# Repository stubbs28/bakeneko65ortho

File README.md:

# bakeneko65ortho
 ortholinearish layout for the bakeneko65

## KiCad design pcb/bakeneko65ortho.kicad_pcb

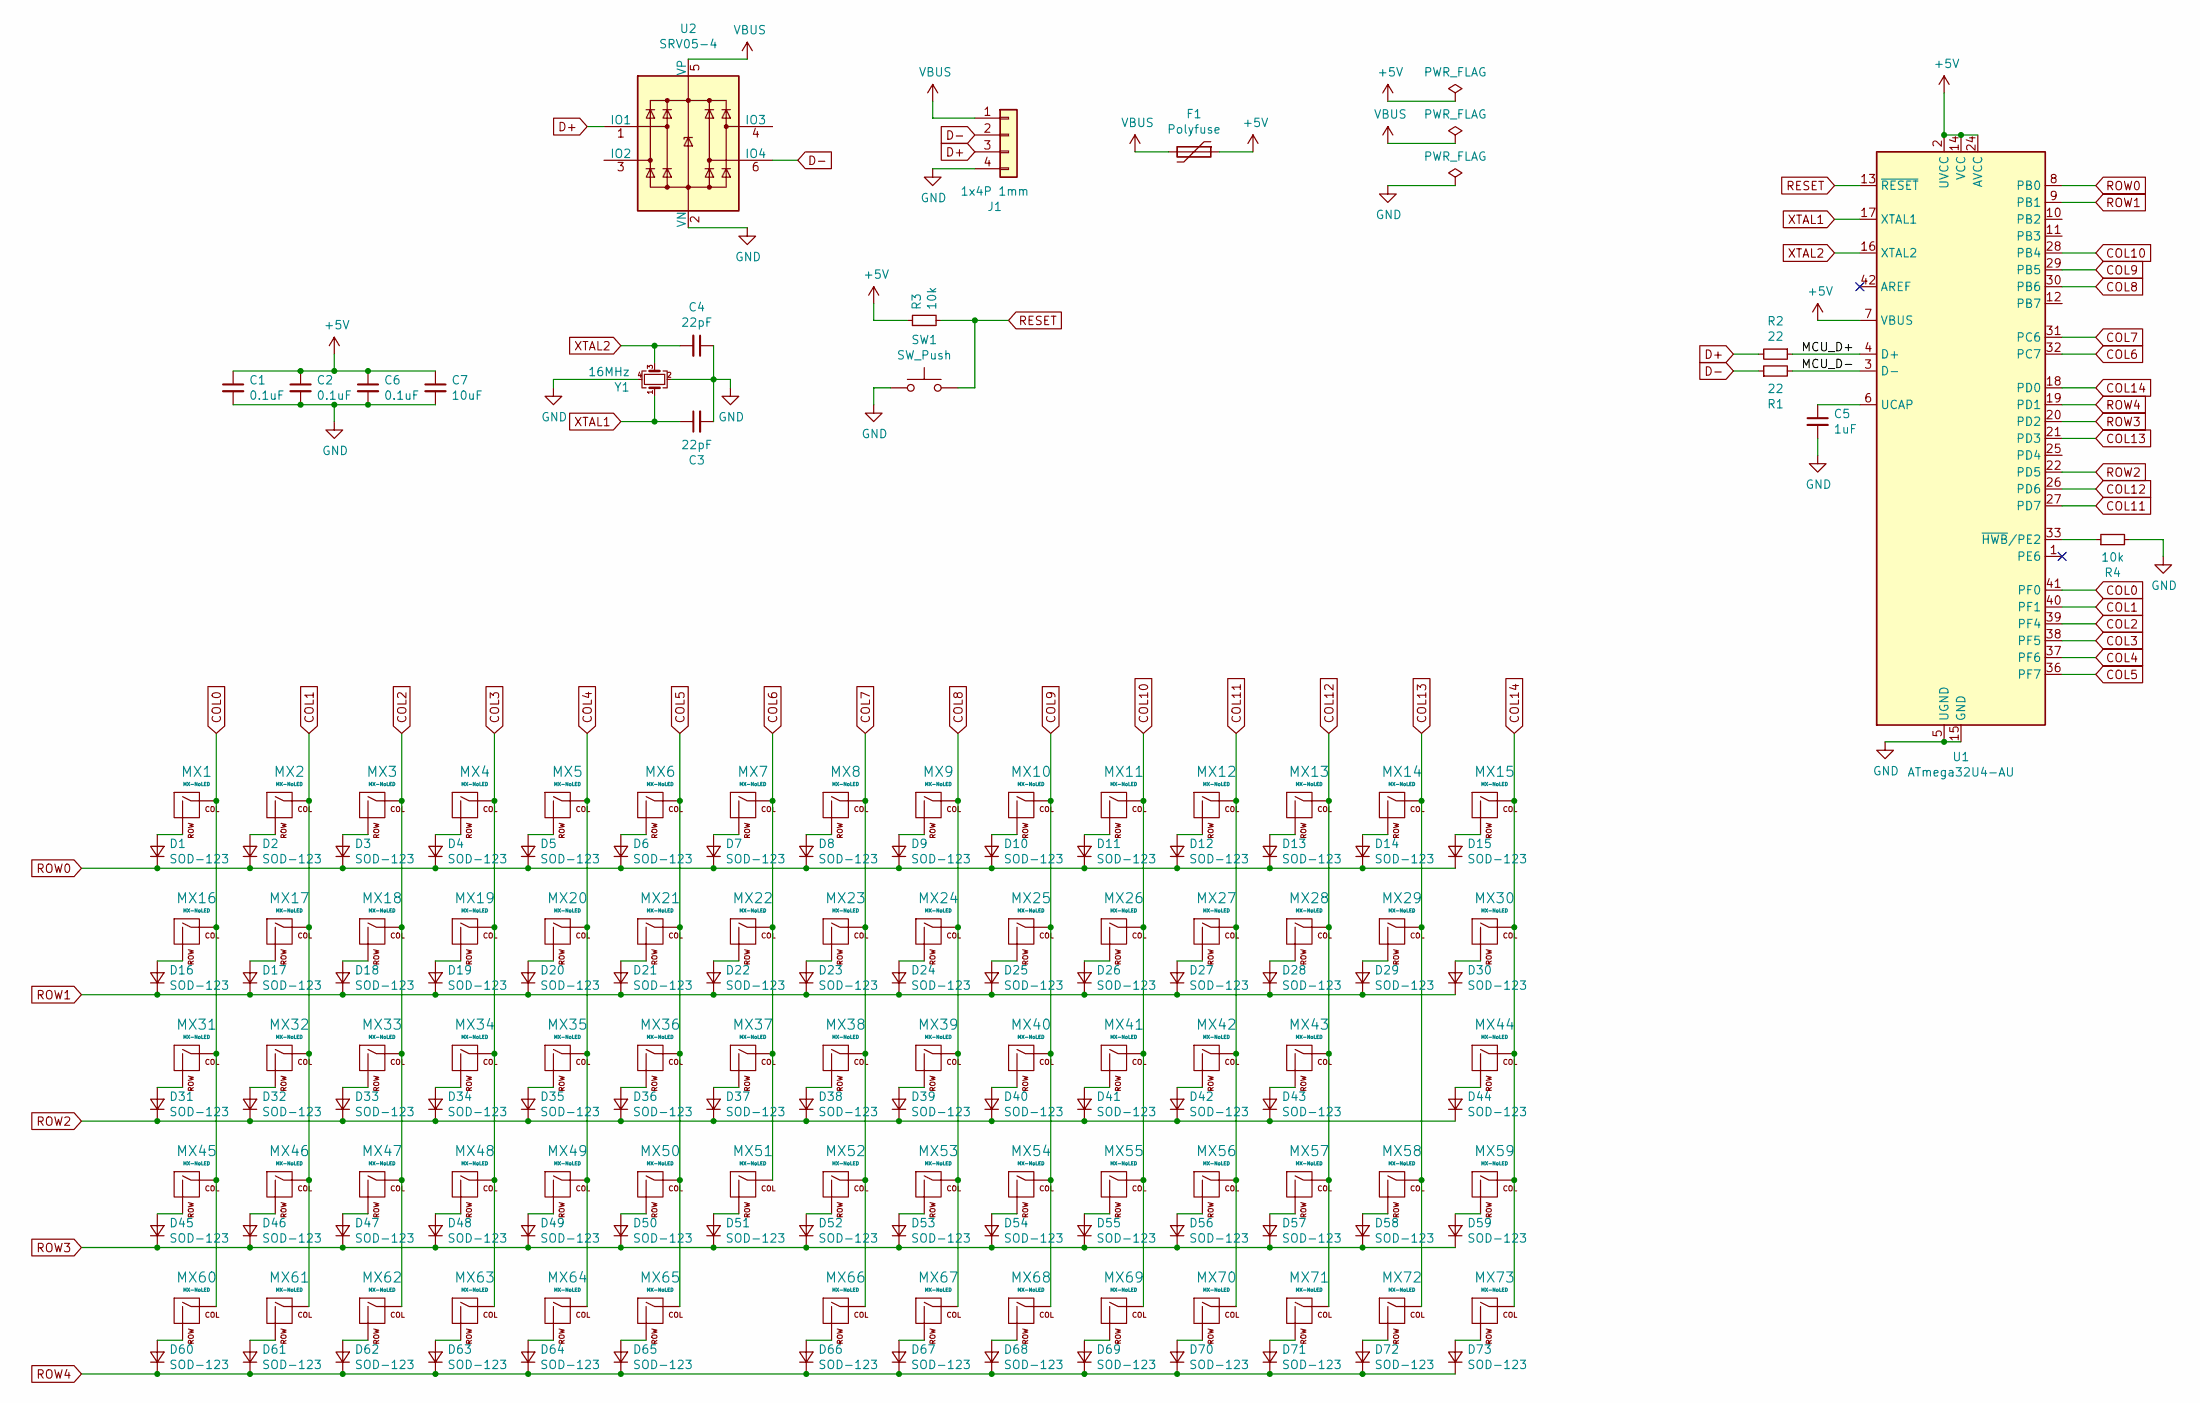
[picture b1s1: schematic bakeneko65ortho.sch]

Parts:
C1, C2, C6: 0.1uF; C_0805_2012Metric
C3, C4: 22pF; C_0805_2012Metric
C5: 1uF; C_0805_2012Metric
C7: 10uF; C_0805_2012Metric
D1, D2, D3, D4, D5, D6, D7, D8, D9, D10, D11, D12, D13, D14, D15, D16, D17, D18, D19, D20, D21, D22, D23, D24, D25, D26, D27, D28, D29, D30, D31, D32, D33, D34, D35, D36, D37, D38, D39, D40, D41, D42, D43, D44, D45, D46, D47, D48, D49, D50, D51, D52, D53, D54, D55, D56, D57, D58, D59, D60, D61, D62, D63, D64, D65, D66, D67, D68, D69, D70, D71, D72, D73: SOD-123; D_SOD-123
F1: Polyfuse; Fuse_1206_3216Metric
J1: 1x4P 1mm; JST_SH_SM04B-SRSS-TB_1x04-1MP_P1.00mm_Horizontal
MX1, MX2, MX3, MX4, MX5, MX6, MX7, MX8, MX9, MX10, MX11, MX12, MX13, MX15, MX16, MX17, MX18, MX19, MX20, MX21, MX22, MX23, MX24, MX25, MX26, MX27, MX28, MX31, MX32, MX33, MX34, MX35, MX36, MX37, MX38, MX39, MX40, MX41, MX42, MX45, MX46, MX47, MX48, MX49, MX50, MX51, MX52, MX53, MX54, MX55, MX56, MX58, MX59, MX60, MX61, MX62, MX63, MX64, MX66, MX67, MX69, MX71, MX72, MX73: MX-NoLED; MXOnly-1U-NoLED
MX14: MX-NoLED; MXOnly-2U-NoLED
MX29, MX30: MX-NoLED; MXOnly-1.5U-NoLED
MX43, MX57: MX-NoLED; MXOnly-2.25U-ReversedStabilizers-NoLED
MX44: MX-NoLED; MXOnly-1.75U-NoLED
MX65: MX-NoLED; MXOnly-2U-ReversedStabilizers-NoLED
MX68, MX70: MX-NoLED; MXOnly-1.25U-NoLED
R1, R2: 22; R_0805_2012Metric
R3, R4: 10k; R_0805_2012Metric
SW1: SW_Push; SKQG-1155865
U1: ATmega32U4-AU; TQFP-44_10x10mm_P0.8mm
U2: SRV05-4; SOT-23-6
Y1: 16MHz; Crystal_SMD_3225-4Pin_3.2x2.5mm

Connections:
+5V: C1.1, C2.1, C6.1, C7.1, F1.1, R3.1, U1.2 (UVCC), U1.7 (VBUS), U1.14 (VCC), U1.24 (AVCC), U1.34 (VCC), U1.44 (AVCC)
/MCU_D+: R2.1, U1.4 (D+)
/MCU_D-: R1.2, U1.3 (D-)
COL0: MX1.1 (COL), MX16.1 (COL), MX31.1 (COL), MX45.1 (COL), MX60.1 (COL), U1.41 (PF0)
COL1: MX2.1 (COL), MX17.1 (COL), MX32.1 (COL), MX46.1 (COL), MX61.1 (COL), U1.40 (PF1)
COL2: MX3.1 (COL), MX18.1 (COL), MX33.1 (COL), MX47.1 (COL), MX62.1 (COL), U1.39 (PF4)
COL3: MX4.1 (COL), MX19.1 (COL), MX34.1 (COL), MX48.1 (COL), MX63.1 (COL), U1.38 (PF5)
COL4: MX5.1 (COL), MX20.1 (COL), MX35.1 (COL), MX49.1 (COL), MX64.1 (COL), U1.37 (PF6)
COL5: MX6.1 (COL), MX21.1 (COL), MX36.1 (COL), MX50.1 (COL), MX65.1 (COL), U1.36 (PF7)
COL6: MX7.1 (COL), MX22.1 (COL), MX37.1 (COL), MX51.1 (COL), U1.32 (PC7)
COL7: MX8.1 (COL), MX23.1 (COL), MX38.1 (COL), MX52.1 (COL), MX66.1 (COL), U1.31 (PC6)
COL8: MX9.1 (COL), MX24.1 (COL), MX39.1 (COL), MX53.1 (COL), MX67.1 (COL), U1.30 (PB6)
COL9: MX10.1 (COL), MX25.1 (COL), MX40.1 (COL), MX54.1 (COL), MX68.1 (COL), U1.29 (PB5)
COL10: MX11.1 (COL), MX26.1 (COL), MX41.1 (COL), MX55.1 (COL), MX69.1 (COL), U1.28 (PB4)
COL11: MX12.1 (COL), MX27.1 (COL), MX42.1 (COL), MX56.1 (COL), MX70.1 (COL), U1.27 (PD7)
COL12: MX13.1 (COL), MX28.1 (COL), MX43.1 (COL), MX57.1 (COL), MX71.1 (COL), U1.26 (PD6)
COL13: MX14.1 (COL), MX29.1 (COL), MX58.1 (COL), MX72.1 (COL), U1.21 (PD3)
COL14: MX15.1 (COL), MX30.1 (COL), MX44.1 (COL), MX59.1 (COL), MX73.1 (COL), U1.18 (PD0)
D+: J1.3, R2.2, U2.1 (IO1)
D-: J1.2, R1.1, U2.6 (IO4)
GND: C1.2, C2.2, C3.2, C4.1, C5.2, C6.2, C7.2, J1.4, R4.2, SW1.1, U1.5 (UGND), U1.15 (GND), U1.23 (GND), U1.35 (GND), U1.43 (GND), U2.2 (VN), Y1.2, Y1.4
unnamed: C5.1, U1.6 (UCAP)
unnamed: D1.2 (A), MX1.2 (ROW)
unnamed: D2.2 (A), MX2.2 (ROW)
unnamed: D3.2 (A), MX3.2 (ROW)
unnamed: D4.2 (A), MX4.2 (ROW)
unnamed: D5.2 (A), MX5.2 (ROW)
unnamed: D6.2 (A), MX6.2 (ROW)
unnamed: D7.2 (A), MX7.2 (ROW)
unnamed: D8.2 (A), MX8.2 (ROW)
unnamed: D9.2 (A), MX9.2 (ROW)
unnamed: D10.2 (A), MX10.2 (ROW)
unnamed: D11.2 (A), MX11.2 (ROW)
unnamed: D12.2 (A), MX12.2 (ROW)
unnamed: D13.2 (A), MX13.2 (ROW)
unnamed: D14.2 (A), MX14.2 (ROW)
unnamed: D15.2 (A), MX15.2 (ROW)
unnamed: D16.2 (A), MX16.2 (ROW)
unnamed: D17.2 (A), MX17.2 (ROW)
unnamed: D18.2 (A), MX18.2 (ROW)
unnamed: D19.2 (A), MX19.2 (ROW)
unnamed: D20.2 (A), MX20.2 (ROW)
unnamed: D21.2 (A), MX21.2 (ROW)
unnamed: D22.2 (A), MX22.2 (ROW)
unnamed: D23.2 (A), MX23.2 (ROW)
unnamed: D24.2 (A), MX24.2 (ROW)
unnamed: D25.2 (A), MX25.2 (ROW)
unnamed: D26.2 (A), MX26.2 (ROW)
unnamed: D27.2 (A), MX27.2 (ROW)
unnamed: D28.2 (A), MX28.2 (ROW)
unnamed: D29.2 (A), MX29.2 (ROW)
unnamed: D30.2 (A), MX30.2 (ROW)
unnamed: D31.2 (A), MX31.2 (ROW)
unnamed: D32.2 (A), MX32.2 (ROW)
unnamed: D33.2 (A), MX33.2 (ROW)
unnamed: D34.2 (A), MX34.2 (ROW)
unnamed: D35.2 (A), MX35.2 (ROW)
unnamed: D36.2 (A), MX36.2 (ROW)
unnamed: D37.2 (A), MX37.2 (ROW)
unnamed: D38.2 (A), MX38.2 (ROW)
unnamed: D39.2 (A), MX39.2 (ROW)
unnamed: D40.2 (A), MX40.2 (ROW)
unnamed: D41.2 (A), MX41.2 (ROW)
unnamed: D42.2 (A), MX42.2 (ROW)
unnamed: D43.2 (A), MX43.2 (ROW)
unnamed: D44.2 (A), MX44.2 (ROW)
unnamed: D45.2 (A), MX45.2 (ROW)
unnamed: D46.2 (A), MX46.2 (ROW)
unnamed: D47.2 (A), MX47.2 (ROW)
unnamed: D48.2 (A), MX48.2 (ROW)
unnamed: D49.2 (A), MX49.2 (ROW)
unnamed: D50.2 (A), MX50.2 (ROW)
unnamed: D51.2 (A), MX51.2 (ROW)
unnamed: D52.2 (A), MX52.2 (ROW)
unnamed: D53.2 (A), MX53.2 (ROW)
unnamed: D54.2 (A), MX54.2 (ROW)
unnamed: D55.2 (A), MX55.2 (ROW)
unnamed: D56.2 (A), MX56.2 (ROW)
unnamed: D57.2 (A), MX57.2 (ROW)
unnamed: D58.2 (A), MX58.2 (ROW)
unnamed: D59.2 (A), MX59.2 (ROW)
unnamed: D60.2 (A), MX60.2 (ROW)
unnamed: D61.2 (A), MX61.2 (ROW)
unnamed: D62.2 (A), MX62.2 (ROW)
unnamed: D63.2 (A), MX63.2 (ROW)
unnamed: D64.2 (A), MX64.2 (ROW)
unnamed: D65.2 (A), MX65.2 (ROW)
unnamed: D66.2 (A), MX66.2 (ROW)
unnamed: D67.2 (A), MX67.2 (ROW)
unnamed: D68.2 (A), MX68.2 (ROW)
unnamed: D69.2 (A), MX69.2 (ROW)
unnamed: D70.2 (A), MX70.2 (ROW)
unnamed: D71.2 (A), MX71.2 (ROW)
unnamed: D72.2 (A), MX72.2 (ROW)
unnamed: D73.2 (A), MX73.2 (ROW)
unnamed: R4.1, U1.33 (~HWB~/PE2)
RESET: R3.2, SW1.2, U1.13 (~RESET)
ROW0: D1.1 (K), D2.1 (K), D3.1 (K), D4.1 (K), D5.1 (K), D6.1 (K), D7.1 (K), D8.1 (K), D9.1 (K), D10.1 (K), D11.1 (K), D12.1 (K), D13.1 (K), D14.1 (K), D15.1 (K), U1.8 (PB0)
ROW1: D16.1 (K), D17.1 (K), D18.1 (K), D19.1 (K), D20.1 (K), D21.1 (K), D22.1 (K), D23.1 (K), D24.1 (K), D25.1 (K), D26.1 (K), D27.1 (K), D28.1 (K), D29.1 (K), D30.1 (K), U1.9 (PB1)
ROW2: D31.1 (K), D32.1 (K), D33.1 (K), D34.1 (K), D35.1 (K), D36.1 (K), D37.1 (K), D38.1 (K), D39.1 (K), D40.1 (K), D41.1 (K), D42.1 (K), D43.1 (K), D44.1 (K), U1.22 (PD5)
ROW3: D45.1 (K), D46.1 (K), D47.1 (K), D48.1 (K), D49.1 (K), D50.1 (K), D51.1 (K), D52.1 (K), D53.1 (K), D54.1 (K), D55.1 (K), D56.1 (K), D57.1 (K), D58.1 (K), D59.1 (K), U1.20 (PD2)
ROW4: D60.1 (K), D61.1 (K), D62.1 (K), D63.1 (K), D64.1 (K), D65.1 (K), D66.1 (K), D67.1 (K), D68.1 (K), D69.1 (K), D70.1 (K), D71.1 (K), D72.1 (K), D73.1 (K), U1.19 (PD1)
VBUS: F1.2, J1.1, U2.5 (VP)
XTAL1: C3.1, U1.17 (XTAL1), Y1.1
XTAL2: C4.2, U1.16 (XTAL2), Y1.3

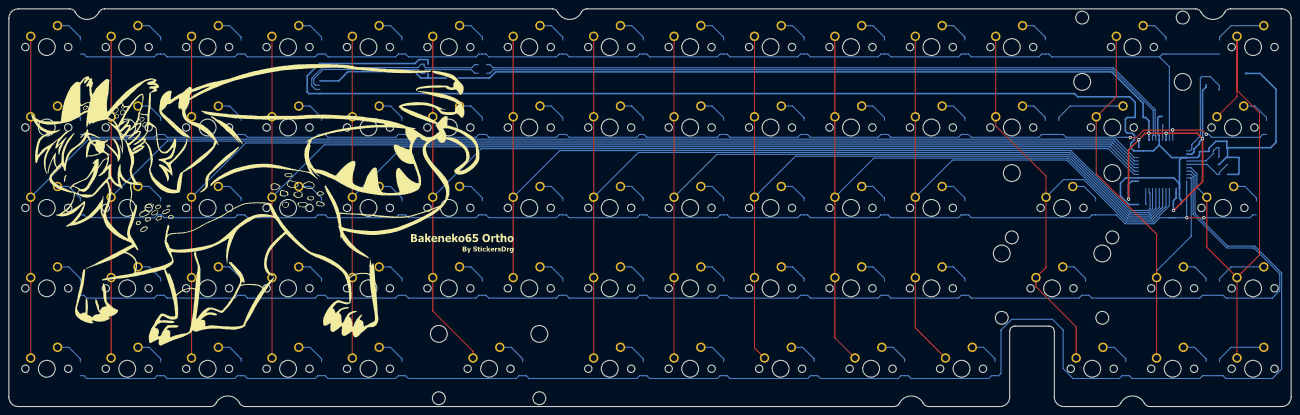
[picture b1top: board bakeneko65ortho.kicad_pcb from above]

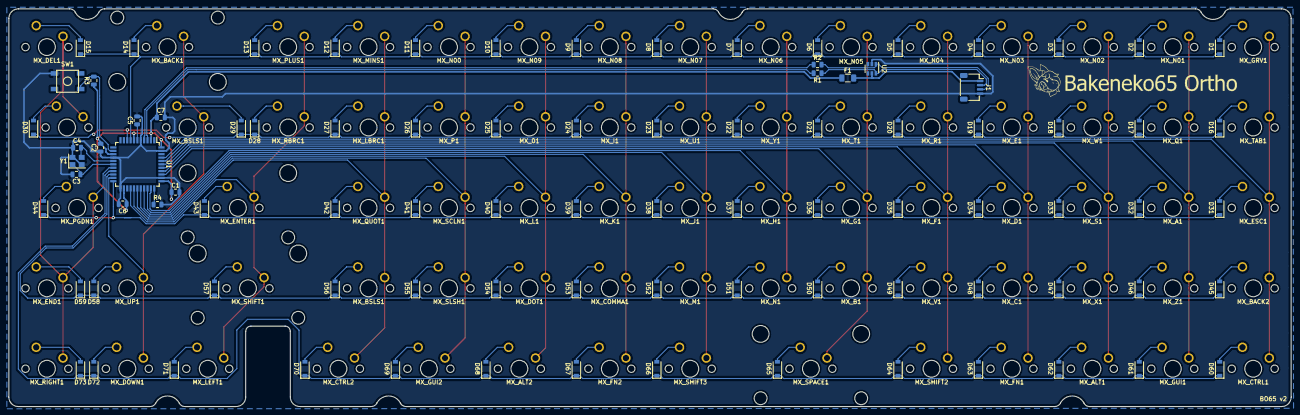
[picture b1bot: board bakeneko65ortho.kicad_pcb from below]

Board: 2 copper layers, 303.8 x 94.2 mm, 163 parts (90 on the bottom side), 105 nets.

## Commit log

2022-05-18 project init
2022-05-18 add submodules
2022-05-18 most of the routing done
2022-05-29 add graphics
2022-06-07 fix broke trace
2022-08-03 add image of assembled keyboard
